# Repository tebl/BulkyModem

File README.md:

# BulkyModem
Back in the old days I, like many others, had a modem. Wasn't quite as old that it used an acoustic coupler, but certainly old enough that it still made exciting clicks when connecting up to things. It also made a lot of horrible shrieking noises when it finally got to talk to an actual computer, if someone else was to pick up the phone while you were using it - you'd usually get to hear a bit of swearing before enjoying the task of doing it all over again. The *BulkyModem* doesn't even hope to do all of those things, but it does allow me to have a go at dialing into a *BBS* from the comforts of my old PCs again. It doesn't do any of that over an analog phone line, because: A) Those no longer exist, and B) We're living in the far distant future, and we now have Wi-Fi!

While there are many options for modems out there that already do the same thing, even quite cool ones that are still being hand-assembled and sold as *Retro WiFi modems* in just about every corner of the world. Or, so I assume anyway. The reason being that if you can find a suitably aged *nerd* tinkering away on their old computer, then they might have been part of the golden age of communication. The other earlier golden age, the one we were talking about before the World Wide Web was unleashed upon the world. Anyway, if you find one of those then there's probably a modem already in their workshop, or possibly in the mail somewhere. So where does my little project fit into all of this? Not sure, but I sure wanted to build one. And the solution I came up with, temporarily fits a very specific spot on my desk.

Where does this one differentiate from the rest of the options then? For that I need to say a bit about my goals when developing it. First off, I wanted to merge old technology with the new - that's not a shocker to anyone who has seen any of my other projects. The second is where this might start becoming of interesting to you, it's the part where I didn't want to build a modem that would only ever work over either *RS-232* - or - attached to a *Commodore 64/128 User Port*. Instead of forcing you to choose, I put a *mode*-button on the front that rewires things between the two modes. Technically that still requires a choice, but did I mention that it was a button? And it's implemented in *hardware*! 

'That's madness', I clearly hear you shouting at the screen. Possibly scaring a cat while you were doing so. Well, it certainly is!

Which is probably the reason for why I started this project all the way back when these retro modems were  still considered a *new* thing, it just took me a while. Mostly because I couldn't get all of it working at the same time. It was never really supposed to work while connected to two different systems at the same time, that would be a whole different bag of crazy - I just wanted the *mode*-button to work as previously advertised. And two years later it mostly does. Turns out that juggling chronic fatigue, *RS-232* signal names and a screaming toddler at the same time, also means that you're bound to strike out quite a few times. My last stumbling block was that I had one ESP8266 development boards that worked perfectly, and five that mostly did nothing. After three revisions I ended up with five that worked with the addition of a simple diode, it was just that without it - I couldn't get anywhere without figuring out how to actually use an oscilloscope. The twist at the end was that the final board that didn't work at the end, wasn't a twist because the working one just kept working. The sixth was just broken from the start, a fact that seems to align with my batting average for cheap development boards.

As for going all the way in order to not require any changes to the firmware, I later added some *optional*. Some of those will require an update to the firmware, if I ever get around to making them. We'll well and truly burn that bridge if I ever get around to crossing it, but for now - just pretend that those don't exist! You didn't need them anyway.

For the project background, all of this started with an article: [Build your own 9600 Baud C64 WiFi Modem For $10](https://1200baud.wordpress.com/2017/03/04/build-your-own-9600-baud-c64-wifi-modem-for-20/). It goes through all of the steps for building a simple version of this with a specially prepared version of the [Zimodem](https://github.com/bozimmerman/Zimodem)-firmware that was made available when the article was written. For a new project that sounds more outdated than retro, I'm going with the shiny new version instead.

- [1> Modules](#1-modules)
  - [1.1> BulkyModem](#11-bulkymodem)
  - [1.3> BulkyModem-32](#13-bulkymodem-32)
  - [1.4> BulkyModem-32 (Mini RS-232)](#14-bulkymodem-32-mini-rs-232)
  - [1.5> BulkyModem Terminal](#15-bulkymodem-terminal)
- [2> Adapters](#2-adapters)
- [3> Acknowledgements](#3-acknowledgements)

# 1> Modules
For the technical details as well as information regarding the devices included in this specific GitHub-project, consult the table below to jump to that particular section. Note that in order to successfully use the *BulkyModem* or *BulkyModem-32* along with a Commodore 64, you will also need the *User Port*-adapter found within the [adapters](#2-adapters)-section.

| Module                             | Description                                      |
| ---------------------------------- | ------------------------------------------------ | 
| [BulkyModem](#11-bulkymodem)       | *BulkyModem*-variant based on ESP8266.
| [BulkyModem-32](#13-bulkymodem-32) | *BulkyModem*-variant based on ESP32.
| [BulkyModem-32 (Mini RS-232)](#14-bulkymodem-32-mini-rs-232) | "Mini"-version of the BulkyModem-32 with an RS-232 interface.
| [BulkyModem Terminal](#15-bulkymodem-terminal) | An instant-on video terminal based on [VersaTerm](https://github.com/dhansel/VersaTerm)

## 1.1> BulkyModem

**Status:** Completed

This is the main module of the project, if you came here looking to build an ESP8266-based retro modem then you've come to the right place. You have the option of going the cheaper route of just building things up on the basic module by itself, consisting only of the main module and nothing else. Alternatively, and this is probably the only reason to build a *BulkyModem* - and that's to build the whole thing as shown above. Note that the list below will include alternate versions of boards, so you need to decide which of them you'll need based on their description.

| Module                 | Required    | Description                        | Documentation                      | Order      |
| ---------------------- | ----------- | ---------------------------------- | ---------------------------------- | ---------- |
| [BulkyModem](https://github.com/tebl/BulkyModem/tree/main/BulkyModem%20Module) | Yes | Main module | [Documentation](https://github.com/tebl/BulkyModem/tree/main/BulkyModem%20Module), [BOM](https://github.com/tebl/BulkyModem/tree/main/BulkyModem%20Module/README.md#3-bom), [Setting it up](https://github.com/tebl/BulkyModem/blob/main/documentation/setting_it_up.md), [Getting started](https://github.com/tebl/BulkyModem/blob/main/documentation/getting_started.md) | [PCBWay](https://www.pcbway.com/project/shareproject/BulkyModem_e6d2ed59.html)
| [BulkyModem Panel](https://github.com/tebl/BulkyModem/tree/main/BulkyModem%20Module%20Panel) | Recommended | Adds a vertical surface for mounting switches and LEDs. | [Documentation](https://github.com/tebl/BulkyModem/tree/main/BulkyModem%20Module%20Panel), [BOM](https://github.com/tebl/BulkyModem/tree/main/BulkyModem%20Module%20Panel/README.md#3-bom) | [PCBWay](https://www.pcbway.com/project/shareproject/BulkyModem_Panel_a5862704.html)
| :repeat_one: [BulkyModem Panel B](https://github.com/tebl/BulkyModem/tree/main/BulkyModem%20Module%20Panel%20B) | Alternative | Similar to above, but uses an RGB LED as a power indicator. Lights up a different colour when in *standby*. | [Documentation](https://github.com/tebl/BulkyModem/tree/main/BulkyModem%20Module%20Panel%20B), [BOM](https://github.com/tebl/BulkyModem/tree/main/BulkyModem%20Module%20Panel%20B/README.md#3-bom) | PCBWay
| [BulkyModem Front faceplate (FP3)](https://github.com/tebl/BulkyModem/tree/main/faceplates/BulkyModem%20FP3) | Recommended | Decorative front panel, mounts on either of the front panels. Has a more futuristic design. | [Documentation](https://github.com/tebl/BulkyModem/tree/main/faceplates/BulkyModem%20FP3) | [PCBWay](https://www.pcbway.com/project/shareproject/BulkyModem_Faceplate_FP3_e1a3cebd.html)
| :repeat_one: [BulkyModem Front faceplate (FP2)](https://github.com/tebl/BulkyModem/tree/main/faceplates/BulkyModem%20FP2) | Alternative | Decorative front panel, mounts on either of the front panels. Has a more minimalistic design. | [Documentation](https://github.com/tebl/BulkyModem/tree/main/faceplates/BulkyModem%20FP2) | PCBWay
| :repeat_one: [BulkyModem Front faceplate (FP1)](https://github.com/tebl/BulkyModem/tree/main/faceplates/BulkyModem%20FP1) | Alternative | Decorative front panel, mounts on either of the front panels. Shorter version (same as shown above). | [Documentation](https://github.com/tebl/BulkyModem/tree/main/faceplates/BulkyModem%20FP1) | [PCBWay](https://www.pcbway.com/project/shareproject/BulkyModem_Faceplate_FP1_738ec333.html)
| [BulkyModem Top/bottom faceplate (FA1)](https://github.com/tebl/BulkyModem/tree/main/faceplates/BulkyModem%20FA1) | Recommended | Decorative faceplate used on the top of the device, can also be used on the bottom in combination with front faceplate [FP2](https://github.com/tebl/BulkyModem/tree/main/faceplates/BulkyModem%20FP2)/[FP3](https://github.com/tebl/BulkyModem/tree/main/faceplates/BulkyModem%20FP3). | [Documentation](https://github.com/tebl/BulkyModem/tree/main/faceplates/BulkyModem%20FA1) | [PCBWay](https://www.pcbway.com/project/shareproject/BulkyModem_Faceplate_FA1_2696aeda.html)

**NB!** Make sure to follow the links for each of the modules, especially when you're looking into ordering the parts needed to complete the device that you want to build. Those modules are listed with their own link to a BOM, or at least what I would call one. Also keep in mind that to use this with a Commodore 64, you need the *User Port*-adapter that's found in the [adapters](#2-adapters)-section.

## 1.3> BulkyModem-32

**Status:** Working, documentation missing

The *BulkyModem-32* is a variant of the modem based on the ESP32, offering some additional features when compared to the [BulkyModem](#11-bulkymodem) that was based on the older and more limited ESP8266. More specifically you'll have access to several additional commands and protocols when using this variant, it also includes an SD-card slot so that you can transfer files between the computer and the modem.

For building one of these things you have the option of going the cheaper route of just using the main PCB, leaving you with the main module and nothing else. Alternatively, and this is probably the only reason why you'd want to build a *BulkyModem* - and that's to go for the whole thing as shown above. Note that there will be alternate versions of some of these boards, so you'll need to decide which of them you want based on their description.

| Module                 | Required    | Description                        | Documentation                      | Order      |
| ---------------------- | ----------- | ---------------------------------- | ---------------------------------- | ---------- |
| [BulkyModem-32](https://github.com/tebl/BulkyModem/tree/main/BulkyModem-32%20Module) | Yes | Main module | [Documentation](https://github.com/tebl/BulkyModem/tree/main/BulkyModem-32%20Module), [BOM](https://github.com/tebl/BulkyModem/tree/main/BulkyModem-32%20Module/README.md#3-bom), [Setting it up](https://github.com/tebl/BulkyModem/blob/main/documentation/setting_it_up.md), [Getting started](https://github.com/tebl/BulkyModem/blob/main/documentation/getting_started.md) | PCBWay
| [BulkyModem Panel](https://github.com/tebl/BulkyModem/tree/main/BulkyModem%20Module%20Panel) | Recommended | Adds a vertical surface for mounting switches and LEDs. | [Documentation](https://github.com/tebl/BulkyModem/tree/main/BulkyModem%20Module%20Panel), [BOM](https://github.com/tebl/BulkyModem/tree/main/BulkyModem%20Module%20Panel/README.md#3-bom) | [PCBWay](https://www.pcbway.com/project/shareproject/BulkyModem_Panel_a5862704.html)
| :repeat_one: [BulkyModem Panel B](https://github.com/tebl/BulkyModem/tree/main/BulkyModem%20Module%20Panel%20B) | Alternative | Similar to above, but uses an RGB LED as a power indicator. Lights up a different colour when in *standby*. | [Documentation](https://github.com/tebl/BulkyModem/tree/main/BulkyModem%20Module%20Panel%20B), [BOM](https://github.com/tebl/BulkyModem/tree/main/BulkyModem%20Module%20Panel%20B/README.md#3-bom) | PCBWay
| [BulkyModem Front faceplate (FP3)](https://github.com/tebl/BulkyModem/tree/main/faceplates/BulkyModem%20FP3) | Recommended | Decorative front panel, mounts on either of the front panels. Has a more futuristic design. | [Documentation](https://github.com/tebl/BulkyModem/tree/main/faceplates/BulkyModem%20FP3) | [PCBWay](https://www.pcbway.com/project/shareproject/BulkyModem_Faceplate_FP3_e1a3cebd.html)
| :repeat_one: [BulkyModem Front faceplate (FP2)](https://github.com/tebl/BulkyModem/tree/main/faceplates/BulkyModem%20FP2) | Alternative | Decorative front panel, mounts on either of the front panels. Has a more minimalistic design. | [Documentation](https://github.com/tebl/BulkyModem/tree/main/faceplates/BulkyModem%20FP2) | PCBWay
| [BulkyModem Top/bottom faceplate (FB1)](https://github.com/tebl/BulkyModem/tree/main/faceplates/BulkyModem%20FB1) | Recommended | Decorative faceplate used on the top of the device, can also be used on the bottom in combination with front faceplate [FP2](https://github.com/tebl/BulkyModem/tree/main/faceplates/BulkyModem%20FP2)/[FP3](https://github.com/tebl/BulkyModem/tree/main/faceplates/BulkyModem%20FP3). | [Documentation](https://github.com/tebl/BulkyModem/tree/main/faceplates/BulkyModem%20FB1) | PCBWay

**NB!** Make sure to follow the links for each of the modules, especially when you're looking into ordering the parts needed to complete the device that you want to build. Those modules are listed with their own link to a BOM, or at least what I would call one. Also keep in mind that to use this with a Commodore 64, you need the *User Port*-adapter that's found in the [adapters](#2-adapters)-section.

## 1.4> BulkyModem-32 (Mini RS-232)

**Status:** Completed

Working on the ESP-32 version of the BulkyModem, that's the one called BulkyModem-32, I had quite a few questions of how some of the features were meant to function. So in order to start development in a more sensible place than what I'm known for, I set out to make a smaller "Mini"-version with the core functionality before trying to add anything else to it. The ESP32-version has more functionality available to it in the Zimodem-firmware, that you'll have available to you when hooking it up to your vintage computers over RS-232. The connection is a 5-wire setup, using RTS/CTS as hardware flow control.

| Module                 | Required    | Description                        | Documentation                      | Order      |
| ---------------------- | ----------- | ---------------------------------- | ---------------------------------- | ---------- |
| [BulkyModem-32 (Mini RS-232)](https://github.com/tebl/BulkyModem/tree/main/BulkyModem-32%20Mini) | Yes | Main module | [Documentation](https://github.com/tebl/BulkyModem/tree/main/BulkyModem-32%20Mini), [BOM](https://github.com/tebl/BulkyModem/tree/main/BulkyModem-32%20Mini/README.md#3-bom), [Setting it up](https://github.com/tebl/BulkyModem/blob/main/documentation/setting_it_up_mini_rs232.md), [Getting started](https://github.com/tebl/BulkyModem/blob/main/documentation/getting_started.md) | [PCBWay](https://www.pcbway.com/project/shareproject/BulkyModem_32_Mini_RS_232_e6ccfb60.html)

## 1.5> BulkyModem Terminal

**Status:** Working, documentation missing

Building a modem comes with its own set of rewards, and in terms of *RS-232* these are what we will define as being *Data Communications Equipment (DCE)*. The other end, normally what we would think of as a computer, is instead labelled as *Data Terminal Equipment (DTE)*. With *RS-232* we have different wires serving different purposes, so one would have different names on each of these two ends - quite possibly being the reason why this kind of information naturally slides off my brain like water off a duck's back. So naturally I wanted to climb that mountain anyway.

So what does it do then? The idea is that instead of having your homebrew computer such as RC2014, RC6502 and similar living inside a terminal emulator program such as PuTTy or Tera Term on your regular computer, you have something that can do the same except without the distractions of the modern computer. Kind of like the original great devices such as the actual DEC VT101, used to hook up to and talk to early mainframes. For sure, I could have used better examples than what mostly amounts to a bunch of computers hooked up to each other, but I was really looking for something that wasn't just a modem. The point is that you hook up your VGA-monitor, your favorite PS/2 keyboard and then you're free to communicate over serial without notifications, updates and all that. Even if you just put a modem on the end, just so that you could chat on a *BBS*.

How did I manage to do all this? I didn't. What I did was discover that someone had already made one, they did it with everyone's favorite new microcontroller - Raspberry Pi Pico - and dubbed it [VersaTerm](https://github.com/dhansel/VersaTerm). What I did was remove a few features in order to make one that would look really pretty, as well as fit with the overall design of the *BulkyModem*. If you want the whole thing, check out the original project. You'll need to go there in order to grab the firmware to build mine anyway, so you might as well check it out before deciding.

For the build you have the option of going the cheaper route of just building things up on the basic module by itself, consisting only of the main module and nothing else. Alternatively, and this is probably the only reason to build a *BulkyModem Terminal* in the first place, and that's to build the whole thing as shown above. There will be alternate versions of some of the board designs, so you need to decide on which one of them you'll need based on their description below.

| Module                 | Required    | Description                        | Documentation                      | Order      |
| ---------------------- | ----------- | ---------------------------------- | ---------------------------------- | ---------- |
| [BulkyModem Terminal](https://github.com/tebl/BulkyModem/tree/main/BulkyModem%20Terminal) | Yes | Main module | [Documentation](https://github.com/tebl/BulkyModem/tree/main/BulkyModem%20Terminal), [BOM](https://github.com/tebl/BulkyModem/tree/main/BulkyModem%20Terminal/README.md#3-bom) | PCBWay
| [BulkyModem Terminal Panel](https://github.com/tebl/BulkyModem/tree/main/BulkyModem%20Terminal%20Panel) | Recommended | Adds a vertical surface for mounting switches and LEDs. | [Documentation](https://github.com/tebl/BulkyModem/tree/main/BulkyModem%20Terminal%20Panel), [BOM](https://github.com/tebl/BulkyModem/tree/main/BulkyModem%20Terminal%20Panel/README.md#3-bom) | PCBWay
| [BulkyModem Terminal Front faceplate (FP3)](https://github.com/tebl/BulkyModem/tree/main/faceplates/BulkyModem%20Terminal%20FP3) | Recommended | Decorative front panel, mounts on either of the front panels. Has a more futuristic design. | [Documentation](https://github.com/tebl/BulkyModem/tree/main/faceplates/BulkyModem%20Terminal%20FP3) | PCBWay
| [BulkyModem Terminal Top/bottom faceplate (FA1)](https://github.com/tebl/BulkyModem/tree/main/faceplates/BulkyModem%20Terminal%20FA1) | Recommended | Decorative faceplate used on the top of the device, can also be used on the bottom in combination with front faceplate [Terminal FP3](https://github.com/tebl/BulkyModem/tree/main/faceplates/BulkyModem%20Terminal%20FP3). | [Documentation](https://github.com/tebl/BulkyModem/tree/main/faceplates/BulkyModem%20Terminal%20FA1) | PCBWay

# 2> Adapters
Separate from the main modules are several adapters, designed for use with the *BulkyModem*, or *BulkyModem-32*, in combination with various systems. The repository also includes a folder for [schematics](https://github.com/tebl/BulkyModem/tree/main/documentation/schematic) in PDF-format, these will be needed in order to track down any faults you encounter when building up and testing any of the adapters.

| Module                 | Required    | Description                        | Documentation                      | Order      |
| ---------------------- | ----------- | ---------------------------------- | ---------------------------------- | ---------- |
| [Commodore 64/128 UserPort](https://github.com/tebl/BulkyModem/tree/main/BulkyModem%20UserPort%20Adapter) | Recommended | Used to connect with Commodore 64/128 over the User Port | [Documentation](https://github.com/tebl/BulkyModem/tree/main/BulkyModem%20UserPort%20Adapter), [BOM](https://github.com/tebl/BulkyModem/tree/main/BulkyModem%20UserPort%20Adapter#3-bom) | [PCBWay](https://www.pcbway.com/project/shareproject/BulkyModem_Commodore_64_128_UserPort_Adapter_a84c7ef6.html)

**NB!** The repository may contain pieces of modules and adapters not explicitly listed here, if they're not listed then they're a work in progress. Some might be functional, others might blow up something or I simply haven't remembered to update the documentation.

# 3> Acknowledgements
Everything comes from something, in particular when it comes to most of my electronics projects. I mainly build things I would like to own, often doing a re-spin in order to fit my own preferences for style over function. The hardest parts of the designs will already have been provided for by people more knowledgeable in things, at least at a scale that I can't hope to match. As mentioned in the introduction, all of this was originated in an article - [Build your own 9600 Baud C64 WiFi Modem For $10](https://1200baud.wordpress.com/2017/03/04/build-your-own-9600-baud-c64-wifi-modem-for-20/). 

The beating heart at the core of almost all of it, is the [Zimodem](https://github.com/bozimmerman/Zimodem)-firmware that runs on an ESP8266/ESP-32. On the C64-side it does have the ability to run at speeds up to 9600 baud which is something that could be met a bit sniggering today, while people at the time would be looking for the butterfly nets. You see, the C64 didn't have an ACIA. There was apparently supposed to be one, but it was removed in order to save on costs. The favored alternative choice then was to attempt to emulate its function, on a computer limited to running at roughly 1 Mhz. In the end your options for modems was the expensive option at 300 baud, followed up by the ridiculously expensive option running at a blistering 1200 baud. The computer actually communicating at 9600 baud in spite of all commonly accepted limitations, is mind-blowing in its execution. For all the details of what ended up being described as *UP9600*, was initially covered in the article [UP9600: How to Bit-Bang 9600 Baud RS-232 on the C64](https://www.pagetable.com/?p=1656). Even if you don't need all that in order to use it, the article is an interesting feat of engineering. Also, it is one of the only sources that I could find that actually describes how serial on the Commodore 64 actually worked, both now and back then.

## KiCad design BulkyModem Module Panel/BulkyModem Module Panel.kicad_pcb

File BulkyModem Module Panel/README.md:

# BulkyModem Module Panel
This is a front-facing panel for controlling the original *BulkyModem*, alternatively the functionally similar *BulkyModem-32*. The difference between the two being the type of MCU used in its design, but as for a front panel - this is compatible with both. The installation of such a panel will be covered within the documentation for each of those two designs, but the assembly of the panel itself will be covered herein.

A front panel is an optional feature and you could quite possibly build a functional design without it, but I feel that it makes the system a lot more enjoyable to use. Along the way I've also developed a second [B-variant](https://github.com/tebl/BulkyModem/tree/main/BulkyModem%20Module%20Panel%20B) of the panel with its primary difference being the use of an RGB LED in place of the power LED, changing the colour when it is on standby. I do, however, recommend that you stick with this version of it. 

- [1> Building the device](#1-building-the-device)
  - [1.1> Soldering it together](#11-soldering-it-together)
- [2> Schematic](#2-schematic)
- [3> BOM](#3-bom)

# 1> Building the device
Building a device such as this assumes you have at least minor experience soldering things together, recommended is that you at the very least have access to a soldering station with adjustable temperature. If currently available, you should probably start with 60/40 rosin core solder as the lead-free alternatives tends to be a bit harder to work with.

With requirements for basic equipment sorted, we need to talk a bit about what you want to achieve while building this project. The reason I ask is that while you can build a functional *BulkyModem* or *BulkyModem-32* using the main PCB by themselves, you're here because you've been looking into building a more complete version of it. That includes a front panel module as well as additional faceplates that would go on the top, bottom and the front of it. That sounds like a lot, but it's worth it. I promise! 

Now that you've arrived at *concepts of a plan* for what you want to build, we can get started on one of the more expensive step in any build process - shopping! For reference, the most expensive step is probably setting your desk and/or house on fire (don't drink and solder). Anyway, when ready to continue with the whole shopping thing that you've heard so much about - head on over to the [BOM](#3-bom)-section. There you'll find information on the kind of components that you'll need.

While I would have liked to give you specific part numbers for "reputable" electronic part suppliers, I can't afford to shop there personally. So what I do, is to make due with what I can find on sites such as eBay, AliExpress or any other future site that will inevitably seem to sell the same, and quite possibly identical set of cheap Chinese components. The downside for you is that I can't link to a part directly and expect it to stay listed tomorrow, so you'll need to consider their descriptions as *suggested search terms* and not *part numbers* in any accurate sense of the definition.

## 1.1> Soldering it together
The construction of this unit should be fairly straight-forward, just take your time in order to make sure everything goes into place - more or less straight. I usually recommend starting by having a good look at the PCBs, try to figure out where all of the listed components should go and in which orientation. All of this should be clearly marked on the silkscreen, but I'll try to cover most of the questionable bits as we get to them.

**NB!** These pictures were taken when building an earlier revision of the PCB, revision C has the top row of components removed (which also explains why they're missing from the BOM). Sorry about that.

Ignoring the two diodes and single resistor that I've already apologized to you for showing you. They're no longer on your PCB, and so you can't install them. Easiest step *ever*!

The first thing you actually get to install is the some right-angle pin headers, and while you're probably an expert at installing such things - the important bit, is to notice is that we need install it on the reverse-side of the PCB! As for the alignment we have a need for it to sit flush against the PCB, so if possible - start by soldering in the opposing corners. Then reheat and push the plastic body of it flush against the board. Just as an FYI; maybe not touch the same piece of metal as that will heat up quite significantly.

As for my next trick, I'm showing you how to install 10mm hex standoffs to each of the four corners (illustrated using a similar, but not exactly the same PCB as shown earlier). The hex shape needs to be rotated so that a flat edge lines up with the left and right edges of the PCB, the reason for this will become evident when we finally attempt to install it onto the main module.

The latching switches used should be as shown, in particular you should make sure that the colour of them match up. Seemingly identical switches with a blue base has shown up in my workshop from time to time, but they have a different pinout and won't work with this board design. Looking at the underside of it, you should notice that there's a rectangular hole that's further towards one side of it - this is the same rectangle that's marked on the PCB. While the pictures don't include it, I recommend both picking up and then installing the  black keycaps onto them. Actually doing that might take a bit of force, but they'll usually go on without too much of a fight. As for this step you shouldn't solder anything, just insert them into the correct orientation.

The front panel includes a significant amount of indicator LEDs, and like the switches you should only loosely insert them into place without soldering. While each leg of an LED has a name, I always forget which is which - so I'll just tell you to push the longer one into the round pads at the top. As is evident by the markings on the PCB, one side should also have a slightly flattened edge. Said edge might be bit hard to actually see on some of the extremely cheap LEDs I've seen floating around, so don't look too hard for it if you've been shopping at the same places that I have. With everything still threatening to fall out at any given moment, add your chosen front faceplate onto the top of it all. Fix temporarily into place using some leftover standoffs.

At this point, most of the LEDs should fall into their corresponding cutouts on the front faceplate, at which point you should be able to solder in one leg of each of them at a time. I prefer to reheat them and immediately press down on the other pin, that way I'm certain that each will end up sitting flush against the cutouts before soldering the rest. As for the switches you will need to press against it from the top, or actually the bottom from this angle, so that it also stays flush. The usage of the black keycaps mentioned earlier will ensure that they end up sitting in their correct position, but if needed: solder one pin, ensure that the switch can move freely, and then soldering remaining pins.

As for the remaining tasks, I've just cut off the excess from the LED pins before replacing all temporary standoffs with screws. As for this part of the assembly, I think that just about wraps it up. The actual installation of the module will be covered in the relevant part of the document for assembling either the [BulkyModem](https://github.com/tebl/BulkyModem/tree/main/BulkyModem%20Module), or alternatively the [BulkyModem-32](https://github.com/tebl/BulkyModem/tree/main/BulkyModem-32%20Module).

# 2> Schematic
The supplied KiCad files should be sufficient as both a schematic and as a  starting point for ordering PCBs. Most if not all fabrication companies will expect Gerber-files, these are generated from KiCAD though you will be able to bypass this step by using PCBway shared projects. As for the schematic, one has been provided for you in [PDF-format](https://github.com/tebl/BulkyModem/tree/main/documentation/schematic) - an important source of information when things inevitably fail to work as advertised.

# 3> BOM
Most parts should be easy to get a hold of from your favourite local electronic component shop, but given that I don't have access to such shops where I live so everything was based on whatever I could get cheapest from eBay/AliExpress (free shipping, but plan on waiting 3-4 weeks for delivery).

| Reference             | Item                                                              | Count | Order  |
| --------------------- | ----------------------------------------------------------------- | ----- | ------ |
| Panel PCB             | Fabricate using Gerber files                                      |     1 | [PCBWay](https://www.pcbway.com/project/shareproject/BulkyModem_Panel_a5862704.html)
| D1,D2,D10-D15,D17 *1  | 5mm LEDs                                                          |     9 |
| J1                    | Breakable right-angle pin header                                  |     1 |
| SW1,SW2               | 6pin 8.5mm x 8.5mm latching switch (including keycap)             |     2 |
| Mounting *2           | Nylon M3 hex standoffs 10mm (M-F)                                 |     4 |
| Mounting *2           | Nylon M3x6mm nylon screws                                         |     4 |
| Mounting *2           | Nylon M3x6mm nylon nuts                                           |     4 |

1) I highly recommend using frosted LEDs, but if you can only find clear ones then you could always frost them a bit yourself using sandpaper or some sort of polishing tool. Personally I prefer using two sets of colours, one for POW/RS-232/C64 and another for the rest. Do note that the corresponding resistor on the main unit must be sized accordingly to differences in colour, or just plain preferences.
2) These are available in the form of kits usually advertised *M3 nylon standoff kit* which should contain most of what you'd need. I do however recommend that you pick up extra M-F standoffs of lengths 10mm and 20mm, as quite a lot of them will be used when building more than one complete module.

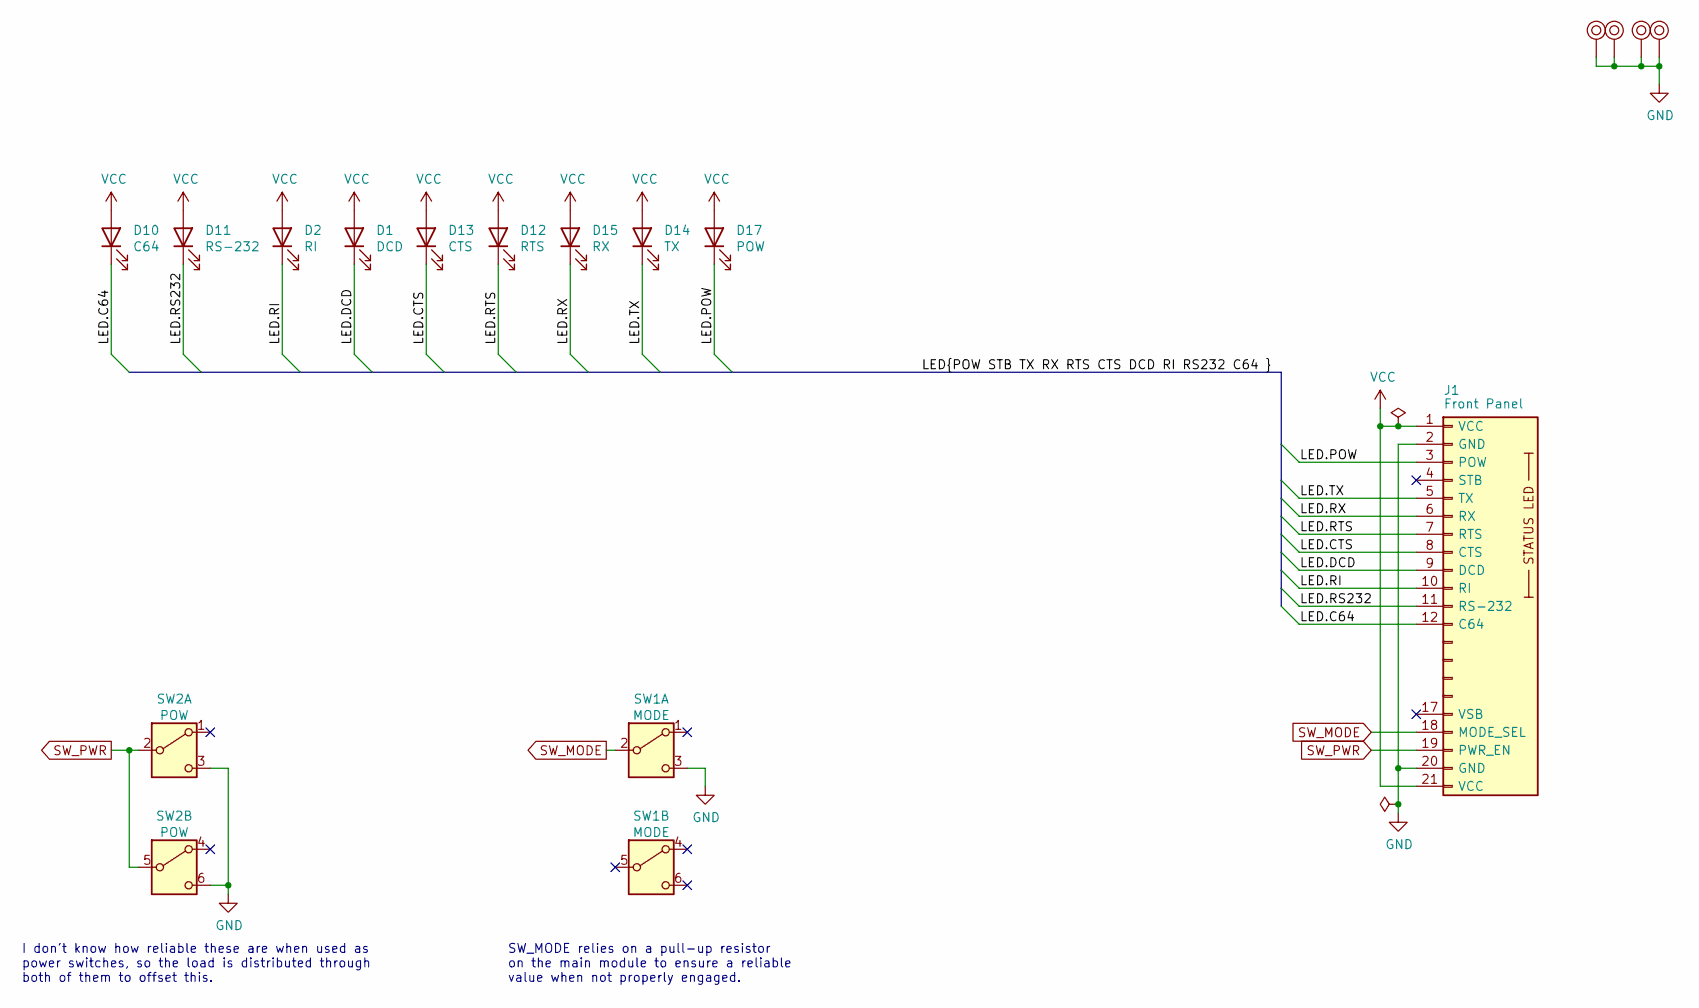
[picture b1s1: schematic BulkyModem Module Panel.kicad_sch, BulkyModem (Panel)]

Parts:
D1: DCD; LED_D5.0mm
D2: RI; LED_D5.0mm
D10: C64; LED_D5.0mm
D11: RS-232; LED_D5.0mm
D12: RTS; LED_D5.0mm
D13: CTS; LED_D5.0mm
D14: TX; LED_D5.0mm
D15: RX; LED_D5.0mm
D17: POW; LED_D5.0mm
J1: Front Panel; PinHeader_1x21_P2.54mm_Horizontal
M1, M2, M3, M4: Mounting_Pin; M3_pin
SW1: MODE; dpdt_switch_black
SW2: POW; dpdt_switch_black

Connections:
/LED.C64: D10.1 (K), J1.12 (C64)
/LED.CTS: D13.1 (K), J1.8 (CTS)
/LED.DCD: D1.1 (K), J1.9 (DCD)
/LED.POW: D17.1 (K), J1.3 (POW)
/LED.RI: D2.1 (K), J1.10 (RI)
/LED.RS232: D11.1 (K), J1.11 (RS-232)
/LED.RTS: D12.1 (K), J1.7 (RTS)
/LED.RX: D15.1 (K), J1.6 (RX)
/LED.TX: D14.1 (K), J1.5 (TX)
GND: J1.2 (GND), J1.20 (GND), M1.1, M2.1, M3.1, M4.1, SW1.3 (C), SW2.3 (C), SW2.6 (C)
SW_MODE: J1.18 (MODE_SEL), SW1.2 (B)
SW_PWR: J1.19 (PWR_EN), SW2.2 (B), SW2.5 (B)
VCC: D1.2 (A), D2.2 (A), D10.2 (A), D11.2 (A), D12.2 (A), D13.2 (A), D14.2 (A), D15.2 (A), D17.2 (A), J1.1 (VCC), J1.21 (VCC)

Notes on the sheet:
SW_MODE relies on a pull-up resistor on the main module to ensure a reliable value when not properly engaged.
I don't know how reliable these are when used as power switches, so the load is distributed through both of them to offset this.

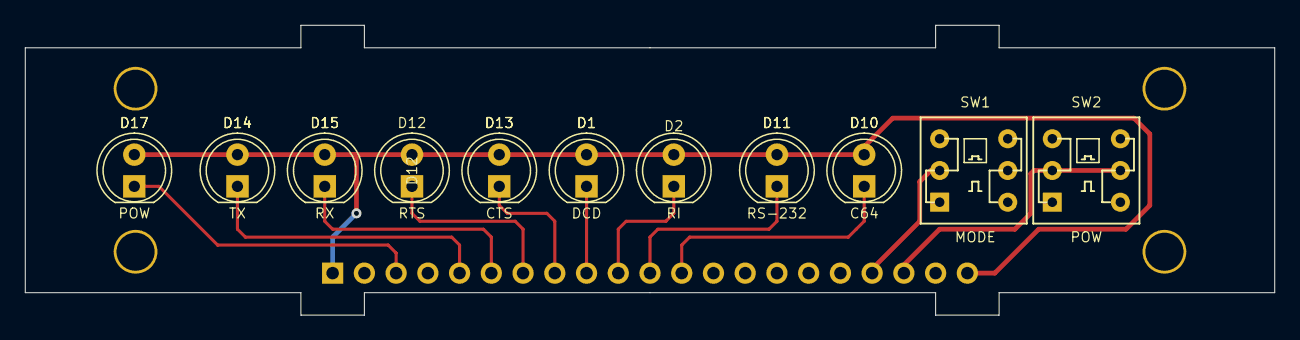
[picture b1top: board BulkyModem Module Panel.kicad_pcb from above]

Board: 2 copper layers, 100.0 x 23.2 mm, 16 parts (1 on the bottom side), 13 nets.

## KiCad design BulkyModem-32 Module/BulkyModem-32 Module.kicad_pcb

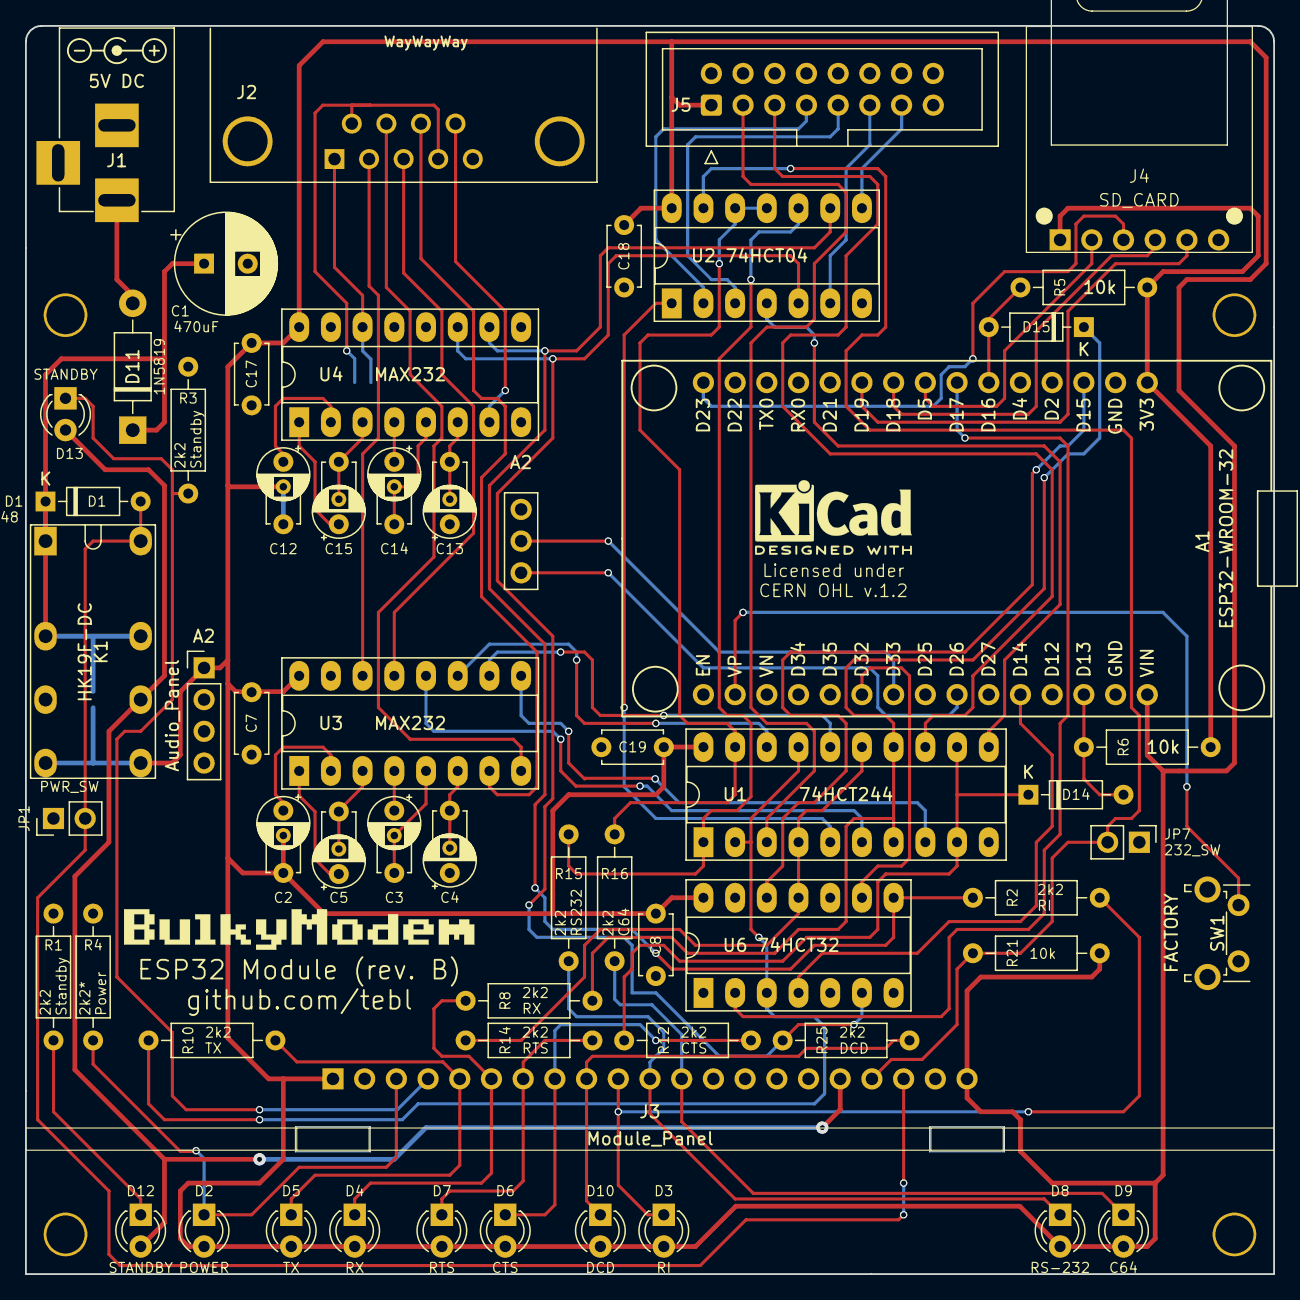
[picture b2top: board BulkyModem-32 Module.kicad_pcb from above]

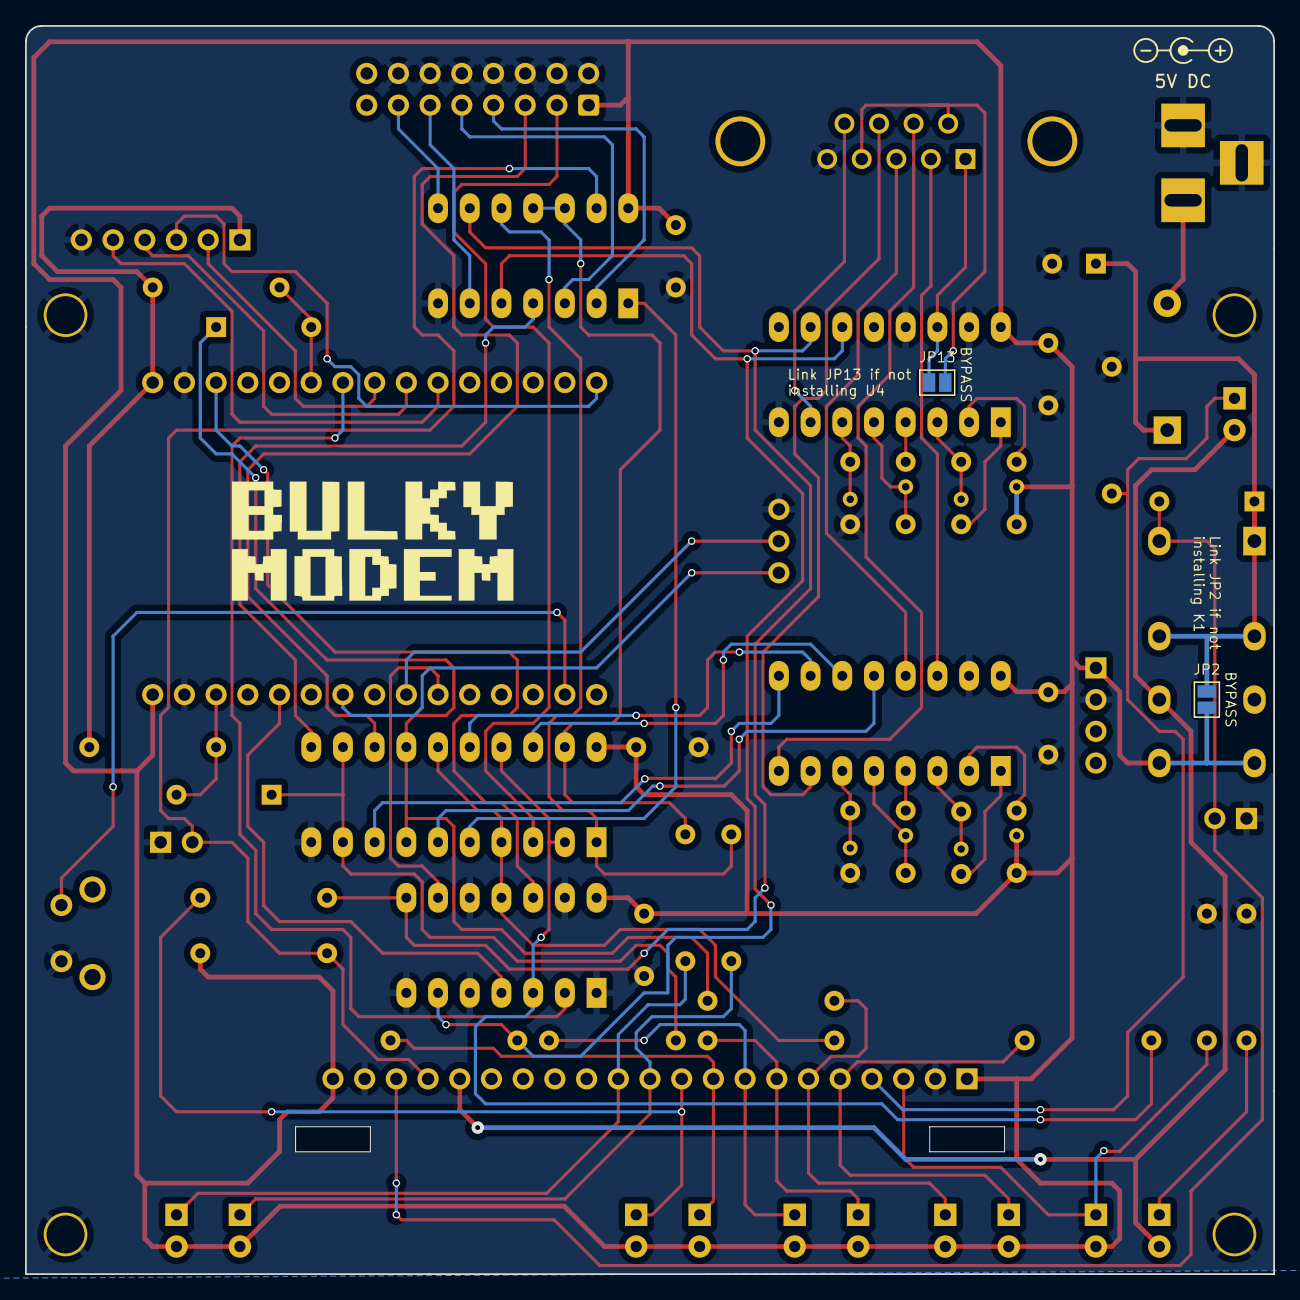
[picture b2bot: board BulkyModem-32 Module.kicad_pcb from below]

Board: 2 copper layers, 100.0 x 100.0 mm, 66 parts (2 on the bottom side), 61 nets.

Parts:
A1: ESP32-WROOM-32; ESP32-WROOM-32D_30
A2: Audio_Panel; AudioModule
C1: 470uF; CP_Radial_D8.0mm_P3.50mm
C2, C3, C4, C5, C12, C13, C14, C15: 1uF; CP_Radial_D4.0mm_P2.00mm_Custom
C7, C8, C17, C18, C19: 100nF; C_Disc_D4.7mm_W2.5mm_P5.00mm
D1, D14, D15: 1N4148; D_DO-35_SOD27_P7.62mm_Horizontal
D2: POWER; LED_D3.0mm
D3: RI; LED_D3.0mm
D4: RX; LED_D3.0mm
D5: TX; LED_D3.0mm
D6: CTS; LED_D3.0mm
D7: RTS; LED_D3.0mm
D8: RS-232; LED_D3.0mm
D9: C64; LED_D3.0mm
D10: DCD; LED_D3.0mm
D11: 1N5819; D_DO-41_SOD81_P10.16mm_Horizontal
D12, D13: STANDBY; LED_D3.0mm
J1: DC IN; BARREL_JACK
J2: DCE; DSUB-9_Female_Horizontal_P2.77x2.84mm_EdgePinOffset7.70mm_H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
J3: Module_Panel
J4: SD_CARD; ESP32_SD_Module
J5: C64_Modem_OUT; UserPort_Adapter_IDC
JP1: PWR_SW; PinHeader_1x02_P2.54mm_Vertical
JP2, JP13: BYPASS; SolderJumper-2_P1.3mm_Open_Pad1.0x1.5mm
JP7: 232_SW; PinHeader_1x02_P2.54mm_Vertical
K1: HK19F-DC
M1, M2, M3, M4: Mounting; M3_pin
R1, R2, R3, R8, R10, R12, R14, R15, R16, R25: 2k2; R_Axial_DIN0207_L6.3mm_D2.5mm_P10.16mm_Horizontal
R4: 2k2*; R_Axial_DIN0207_L6.3mm_D2.5mm_P10.16mm_Horizontal
R5, R6, R21: 10k; R_Axial_DIN0207_L6.3mm_D2.5mm_P10.16mm_Horizontal
SW1: FACTORY; SW_Tactile_SPST_Angled_PTS645Vx39-2LFS
SYM1: DC_5V; PWR_Specification
U1: 74HCT244; DIP-20_W7.62mm_Socket_LongPads
U2: 74HCT04; DIP-14_W7.62mm_Socket_LongPads
U3, U4: MAX232; DIP-16_W7.62mm_Socket_LongPads
U6: 74HCT32; DIP-14_W7.62mm_Socket_LongPads

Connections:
+3.3V: A1.16 (3.3V), J4.1, R5.1, R6.1
+5V: A1.15 (VIN), A2.1 (VCC), C2.2, C7.1, C8.1, C12.2, C17.1, C18.1, C19.1, D2.2 (A), D3.2 (A), D4.2 (A), D5.2 (A), D6.2 (A), D7.2 (A), D8.2 (A), D9.2 (A), D10.2 (A), J3.1 (VCC), J3.21 (VCC), J5.1 (VCC), JP2.2 (B), K1.8 (NO_1), K1.9 (NO_2), R21.2, U1.20 (VCC), U2.14 (VCC), U3.16 (VCC), U4.16 (VCC), U6.14 (VCC)
/232_CTS: U1.8 (1A3), U3.9 (R2OUT)
/232_RTS: U1.16 (1Y1), U3.10 (T2IN)
/232_RX: U1.6 (1A2), U3.12 (R1OUT)
/232_TX: U1.18 (1Y0), U3.11 (T1IN)
/C64_CTS: U1.11 (2A3), U2.4
/C64_RTS: U1.5 (2Y1), U2.1
/C64_RX: J5.3 (RX), U1.13 (2A2)
/C64_TX: J5.2 (TX), U1.3 (2Y0)
/Front Panel/LED_C64: D9.1 (K), J3.12 (C64), R16.2
/Front Panel/LED_CTS: D6.1 (K), J3.8 (CTS), R12.2
/Front Panel/LED_DCD: D10.1 (K), J3.9 (DCD), R25.2
/Front Panel/LED_POW: D2.1 (K), J3.3 (POW), R4.2
/Front Panel/LED_RI: D3.1 (K), J3.10 (RI), R2.2
/Front Panel/LED_RS232: D8.1 (K), J3.11 (RS-232), R15.2
/Front Panel/LED_RTS: D7.1 (K), J3.7 (RTS), R14.2
/Front Panel/LED_RX: D4.1 (K), J3.6 (RX), R8.2
/Front Panel/LED_STB: D13.1 (K), J3.4 (STB), R3.2
/Front Panel/LED_TX: D5.1 (K), J3.5 (TX), R10.2
/RS-232/SER_CTS: J2.7, U3.8 (R2IN)
/RS-232/SER_DCD: J2.1, JP13.1 (A), U4.14 (T1OUT)
/RS-232/SER_RI: J2.9, U4.7 (T2OUT)
/RS-232/SER_RTS: J2.8, U3.7 (T2OUT)
/RS-232/SER_RxD: J2.3, U3.13 (R1IN)
/RS-232/SER_TxD: J2.2, U3.14 (T1OUT)
AUDIO_RX: A1.9 (D26), A2.5 (AUDIO_TX)
AUDIO_TX: A1.7 (D33), A2.6 (AUDIO_RX)
ESP_CTS: D14.1 (K), R12.1, U1.9 (2Y3), U1.12 (1Y3)
ESP_DCD: R25.1, U2.5, U4.11 (T1IN), U6.6
ESP_RI: R2.1, U2.9, U4.10 (T2IN), U6.8
ESP_RTS: R14.1, U1.4 (1A1), U1.15 (2A1), U6.11
ESP_RX: D15.1 (K), R8.1, U1.7 (2Y2), U1.14 (1Y2)
ESP_TX: R10.1, U1.2 (1A0), U1.17 (2A0), U6.3
GND: A1.14 (GND), A1.17 (GND), A2.2 (GND), A2.7 (GND), C1.2, C4.1, C7.2, C8.2, C13.1, C17.2, C18.2, C19.2, J1.2, J1.3, J2.5, J3.2 (GND), J3.20 (GND), J4.6, J5.9 (GND), J5.10 (GND), J5.11 (GND), J5.12 (GND), J5.13 (GND), J5.14 (GND), J5.15 (GND), JP1.1 (A), JP7.1 (A), M1.1, M2.1, M3.1, M4.1, R1.1, R3.1, R4.1, SW1.2, U1.10 (GND), U2.7 (GND), U3.15 (GND), U4.8 (R2IN), U4.13 (R1IN), U4.15 (GND), U6.1, U6.5, U6.7 (GND), U6.10, U6.13
MODE_232: R15.1, U1.1 (1OE), U2.10
MODE_C64: R16.1, U1.19 (2OE), U2.11, U2.12
MODE_SEL: J3.18 (MODE_SEL), JP7.2 (B), R21.1, U2.13
unnamed: A1.13 (D13), D14.2 (A), R6.2
unnamed: A1.11 (D14), U6.4
unnamed: A1.18 (D15), U6.12
unnamed: A1.21 (D16), D15.2 (A), R5.2
unnamed: A1.22 (D17), U6.2
unnamed: A1.6 (D32), U6.9
unnamed: A1.2 (VP), SW1.1
unnamed: D11.2 (A), J1.1
unnamed: D12.1 (K), R1.2
unnamed: J5.5 (CTS), U2.3
unnamed: J5.6 (DCD), U2.6
unnamed: J5.7 (RI), U2.8
unnamed: J5.4 (RTS), U2.2
unnamed: J2.4, J2.6, JP13.2 (B)
unnamed: C12.1, U4.2 (VS+)
unnamed: C13.2, U4.6 (VS-)
PWR_EN: D1.2 (A), J3.19 (PWR_EN), JP1.2 (B), K1.16
SPI_CLK: A1.24 (D18), J4.4
SPI_CS: A1.23 (D5), J4.2
SPI_MISO: A1.25 (D19), J4.5
SPI_MOSI: A1.30 (D23), J4.3
VIN: C1.1, D1.1 (K), D11.1 (K), JP2.1 (A), K1.1, K1.4 (COM_1), K1.13 (COM_2)
VSB: D12.2 (A), D13.2 (A), J3.17 (VSB), K1.11 (NC_2)

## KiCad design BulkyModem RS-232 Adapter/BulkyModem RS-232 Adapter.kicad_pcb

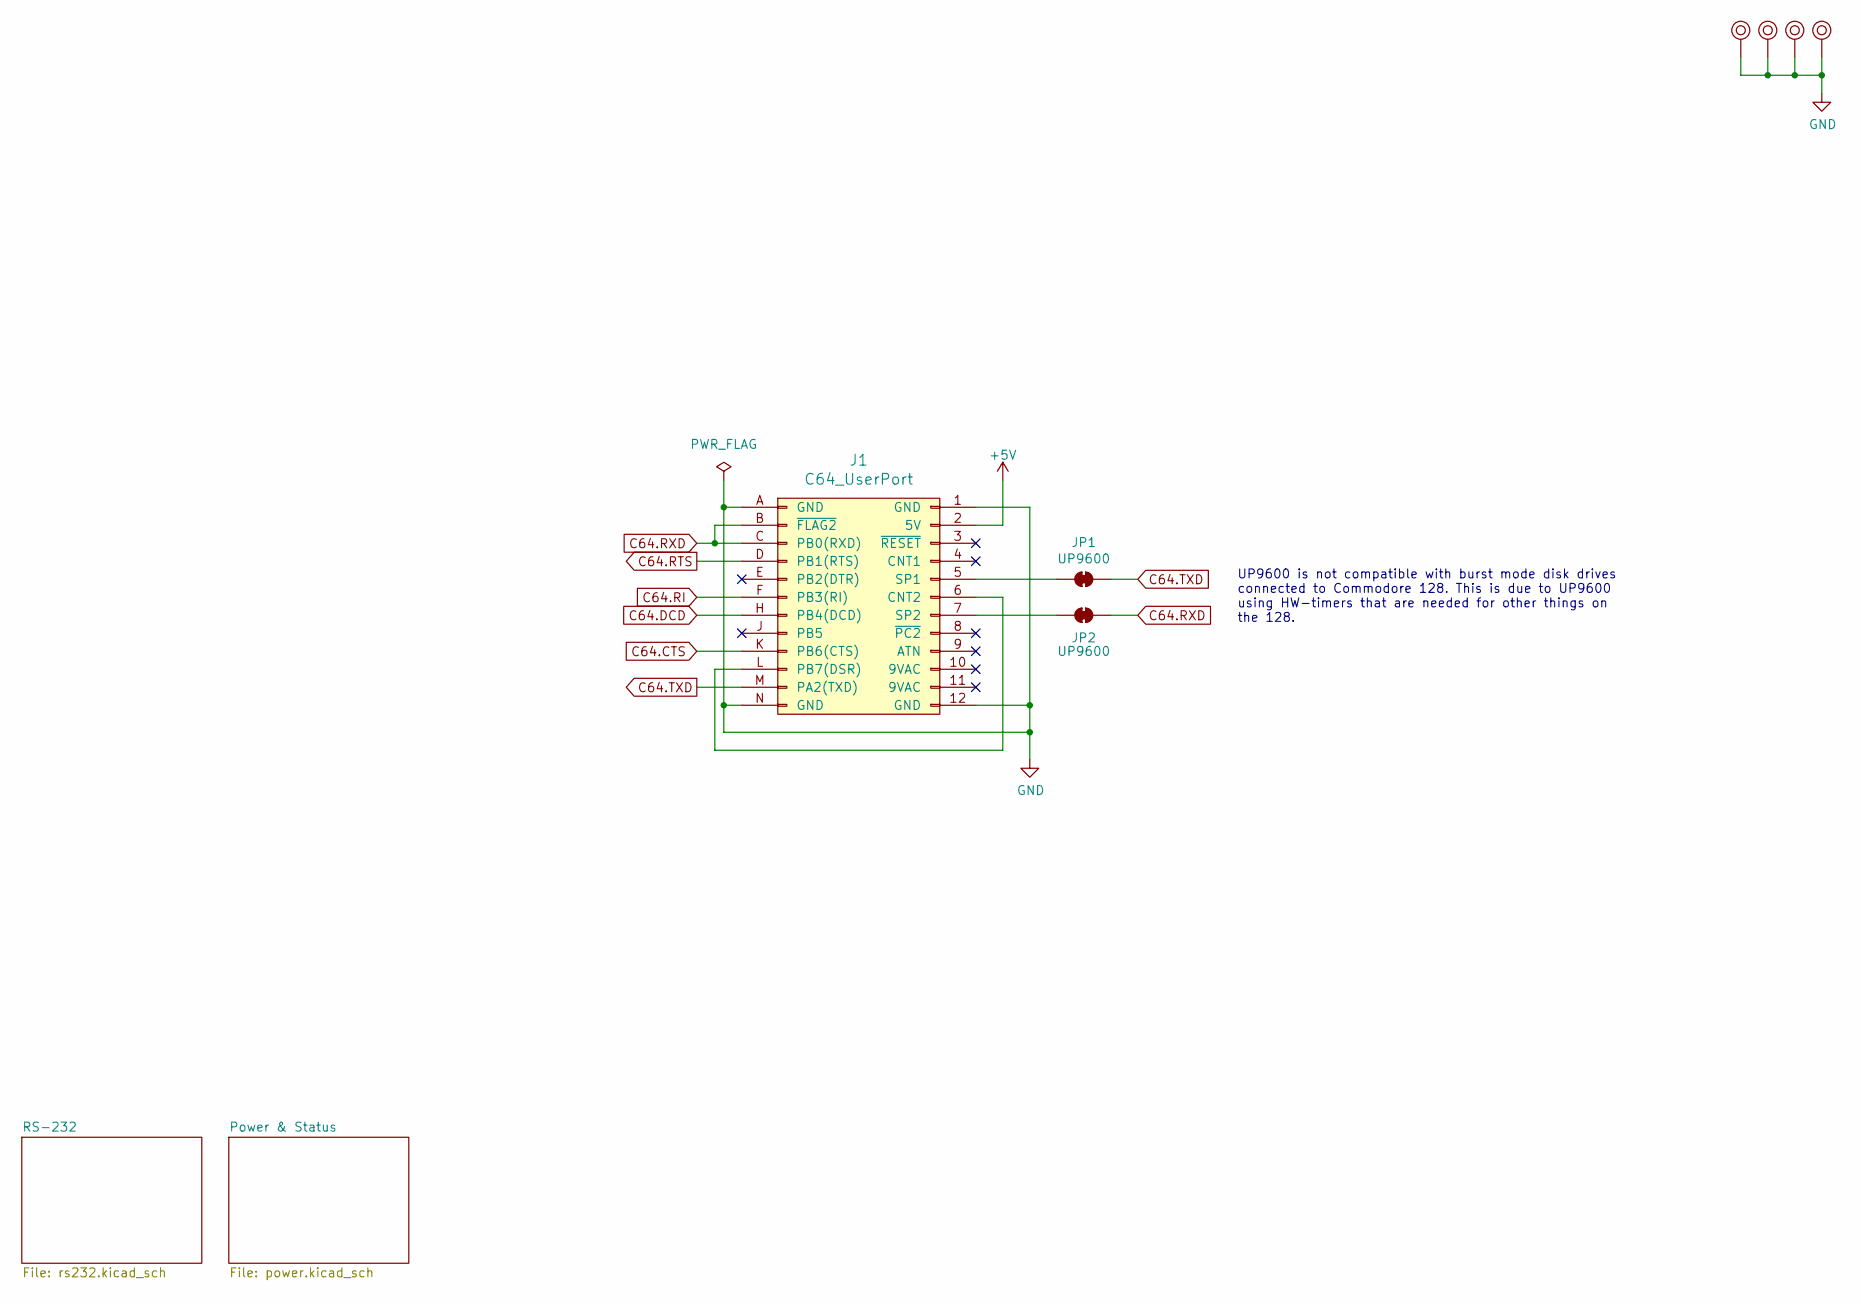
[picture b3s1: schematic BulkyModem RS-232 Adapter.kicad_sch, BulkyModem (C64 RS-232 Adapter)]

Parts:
J1: C64_UserPort; C64_User-Port
JP1, JP2: UP9600; PinHeader_1x02_P2.54mm_Vertical
M1, M2, M3, M4: Mounting; M3_pin

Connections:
+5V: J1.2 (5V); also elsewhere on the board
C64.CTS: J1.K (PB6(CTS)); also elsewhere on the board
C64.DCD: J1.H (PB4(DCD)); also elsewhere on the board
C64.RI: J1.F (PB3(RI)); also elsewhere on the board
C64.RTS: J1.D (PB1(RTS)); also elsewhere on the board
C64.RXD: J1.B (~FLAG2), J1.C (PB0(RXD)), JP2.2 (B); also elsewhere on the board
C64.TXD: J1.M (PA2(TXD)), JP1.2 (B); also elsewhere on the board
GND: J1.1 (GND), J1.12 (GND), J1.A (GND), J1.N (GND), M1.1, M2.1, M3.1, M4.1; also elsewhere on the board
unnamed: J1.6 (CNT2), J1.L (PB7(DSR))
unnamed: J1.5 (SP1), JP1.1 (A)
unnamed: J1.7 (SP2), JP2.1 (A)

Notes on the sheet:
UP9600 is not compatible with burst mode disk drives connected to Commodore 128. This is due to UP9600 using HW-timers that are needed for other things on the 128.

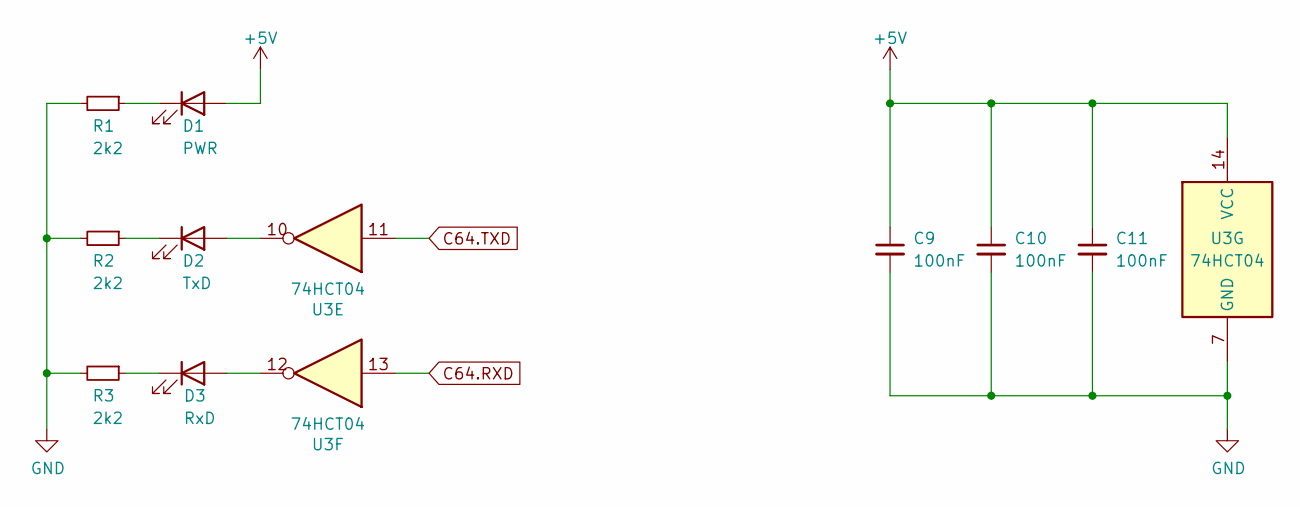
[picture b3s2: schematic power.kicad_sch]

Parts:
C9, C10, C11: 100nF; C_Disc_D4.7mm_W2.5mm_P5.00mm
D1: PWR; LED_D3.0mm
D2: TxD; LED_D3.0mm
D3: RxD; LED_D3.0mm
R1, R2, R3: 2k2; R_Axial_DIN0207_L6.3mm_D2.5mm_P10.16mm_Horizontal
U3: 74HCT04; DIP-14_W7.62mm_Socket_LongPads

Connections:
+5V: C9.1, C10.1, C11.1, D1.2 (A), U3.14 (VCC); also elsewhere on the board
C64.RXD: U3.13; also elsewhere on the board
C64.TXD: U3.11; also elsewhere on the board
GND: C9.2, C10.2, C11.2, R1.2, R2.2, R3.2, U3.7 (GND); also elsewhere on the board
unnamed: D1.1 (K), R1.1
unnamed: D2.2 (A), U3.10
unnamed: D2.1 (K), R2.1
unnamed: D3.2 (A), U3.12
unnamed: D3.1 (K), R3.1

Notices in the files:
BulkyModem Module/BulkyModem Module.kicad_pcb:
Licensed under
CERN OHL v.1.2
BulkyModem RS-232 Adapter/BulkyModem RS-232 Adapter.kicad_pcb:
Licensed under CERN OHL v1.2
